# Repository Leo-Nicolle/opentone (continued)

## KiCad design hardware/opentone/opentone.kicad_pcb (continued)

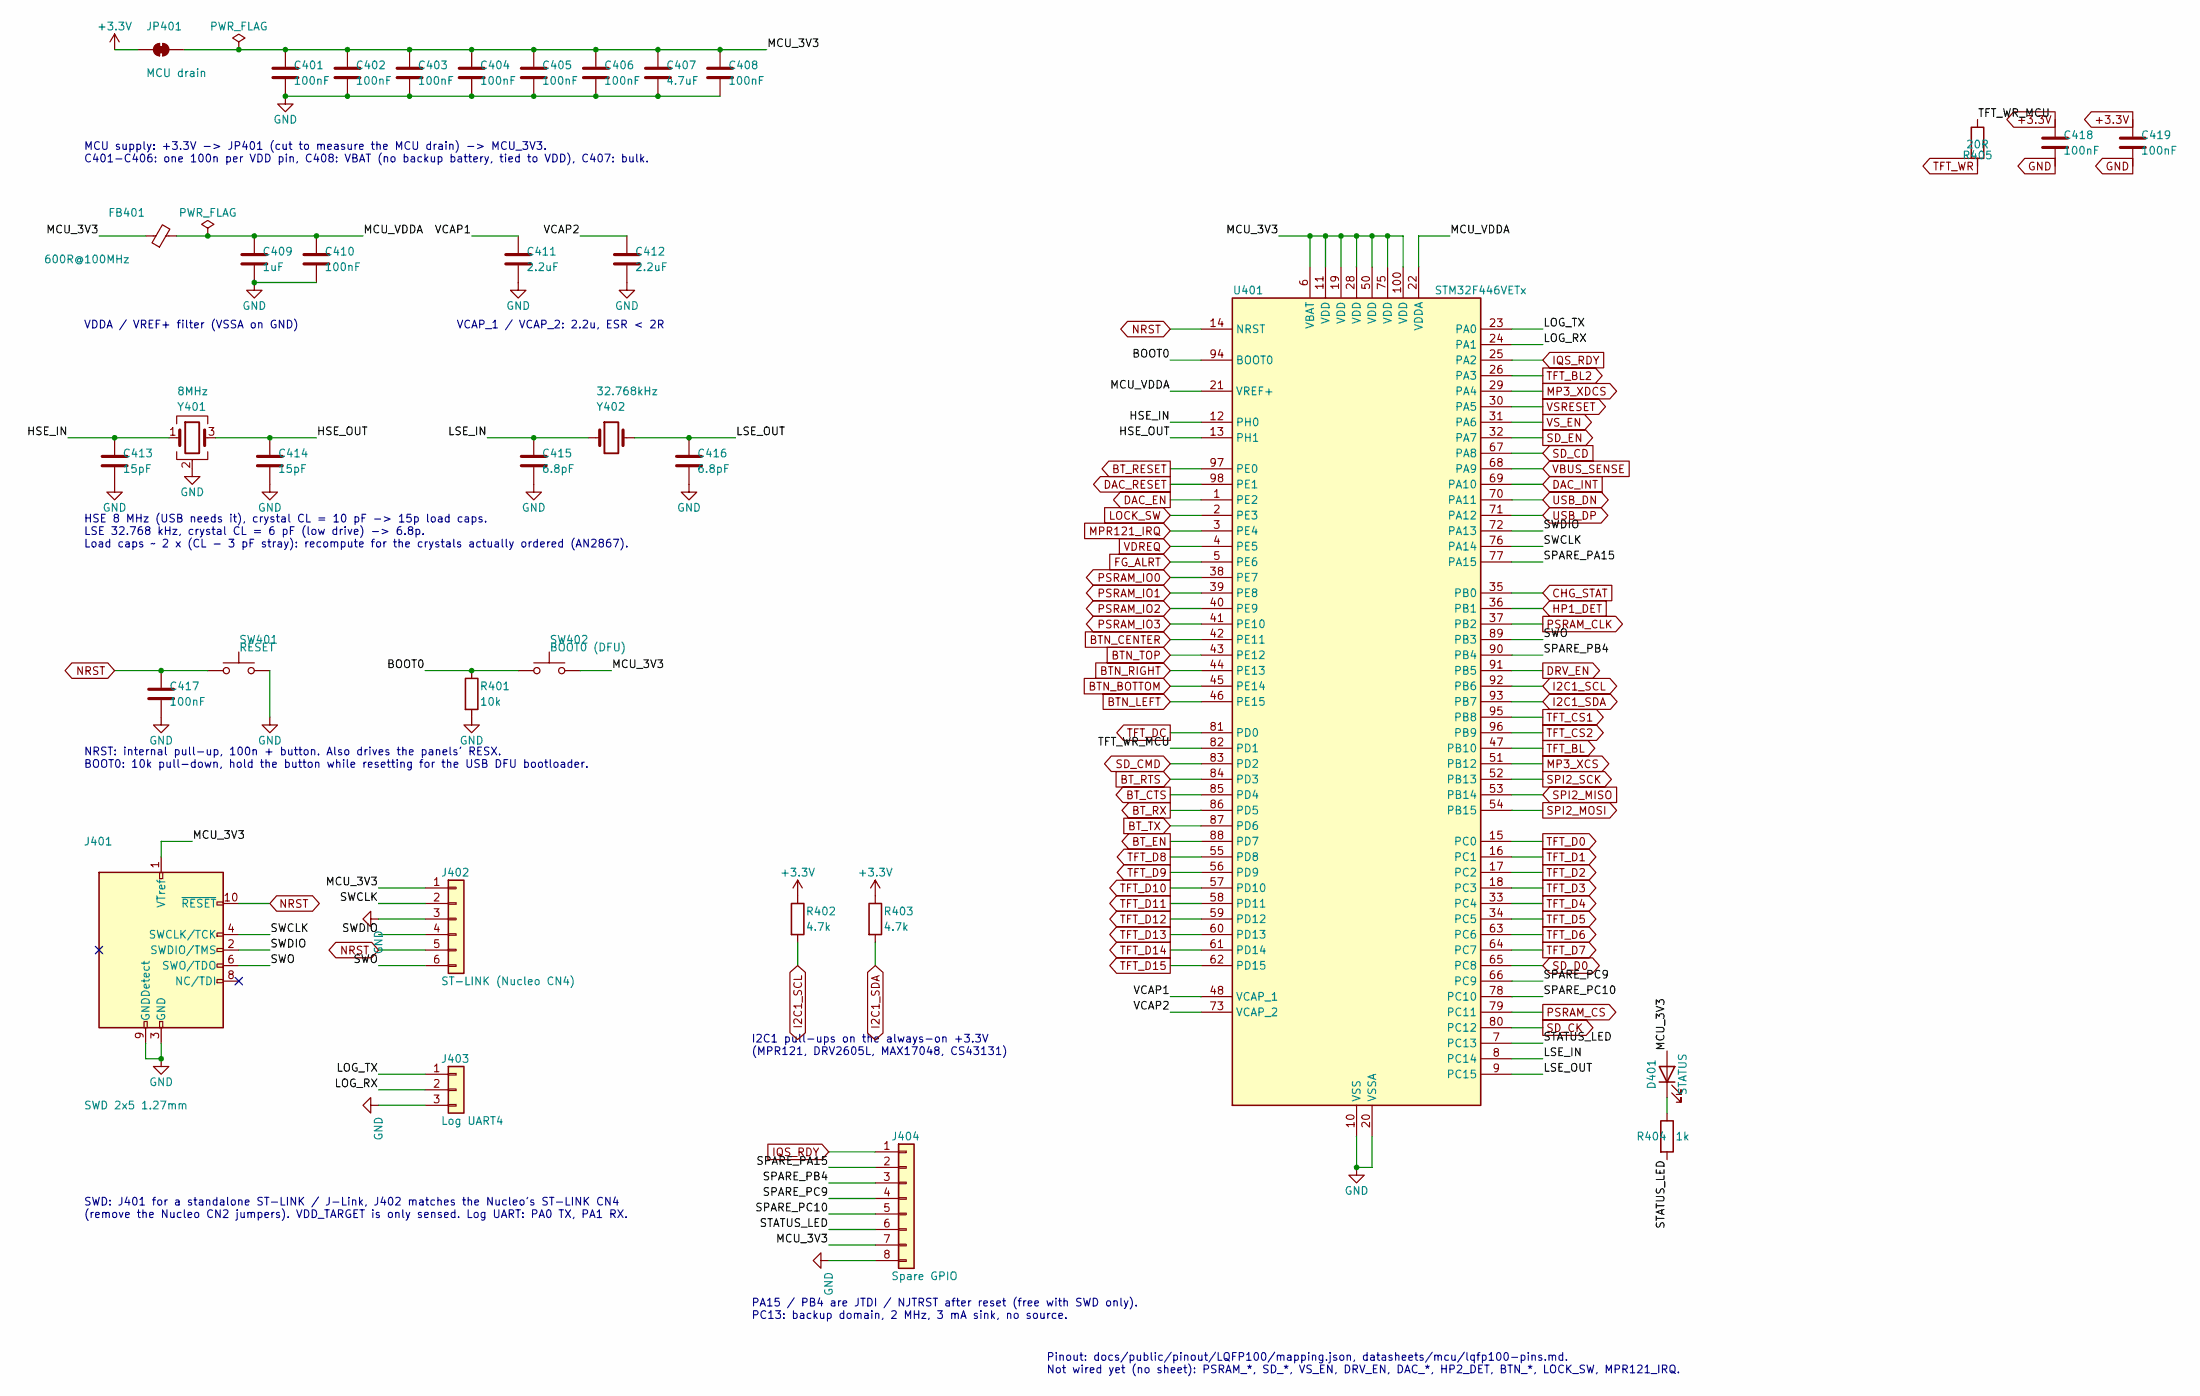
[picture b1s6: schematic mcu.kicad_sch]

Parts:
C401, C402, C403, C404, C405, C406, C408, C410, C417, C418, C419: 100nF; C_0603_1608Metric; Part number CC0603KRX7R9BB104; LCSC C14663
C407: 4.7uF; C_0603_1608Metric; Part number CL10A475KO8NNNC; LCSC C19666
C409: 1uF; C_0603_1608Metric; Part number CL10A105KB8NNNC; LCSC C15849
C411, C412: 2.2uF; C_0603_1608Metric; Part number CL10A225KO8NNNC; LCSC C23630
C413, C414: 15pF; C_0603_1608Metric; Part number CL10C150JB8NNNC; LCSC C1644
C415, C416: 6.8pF; C_0603_1608Metric; Part number 0603CG6R8C500NT; LCSC C1679
D401: STATUS; LED_0603_1608Metric; Part number KT-0603R; LCSC C2286
FB401: 600R@100MHz; L_0603_1608Metric; Part number GZ1608D601TF; LCSC C1002
J401: SWD 2x5 1.27mm; PinHeader_2x05_P1.27mm_Vertical_SMD; Part number 20021121-00010C4LF; LCSC C150517
J402: ST-LINK (Nucleo CN4); PinHeader_1x06_P2.54mm_Vertical
J403: Log UART4; PinHeader_1x03_P2.54mm_Vertical
J404: Spare GPIO; PinHeader_1x08_P2.54mm_Vertical
JP401: MCU drain; SolderJumper-2_P1.3mm_Bridged_RoundedPad1.0x1.5mm
R401: 10k; R_0603_1608Metric; Part number 0603WAF1002T5E; LCSC C25804
R402, R403: 4.7k; R_0603_1608Metric; Part number 0603WAF4701T5E; LCSC C23162
R404: 1k; R_0603_1608Metric; Part number 0603WAF1001T5E; LCSC C21190
R405: 20R; R_0603_1608Metric; Part number 0603WAF200JT5E; LCSC C22950
SW401: RESET; SW_SPST_PTS810; Part number PTS810SJG250SMTRLFS; LCSC C221895
SW402: BOOT0 (DFU); SW_SPST_PTS810; Part number PTS810SJG250SMTRLFS; LCSC C221895
U401: STM32F446VETx; LQFP-100_14x14mm_P0.5mm; Part number STM32F446VET6; LCSC C91929
Y401: 8MHz; Crystal_SMD_3225-4Pin_3.2x2.5mm; Part number K3A080001010; LCSC C19076848
Y402: 32.768kHz; Crystal_SMD_3215-2Pin_3.2x1.5mm; Part number FC-135 32.7680KA-E; LCSC C20340322

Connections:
+3.3V: C418.1, C419.1, JP401.1 (A), R402.1, R403.1; also elsewhere on the board
/MCU/BOOT0: R401.1, SW402.1, U401.94 (BOOT0)
/MCU/HSE_IN: C413.1, U401.12 (PH0), Y401.1
/MCU/HSE_OUT: C414.1, U401.13 (PH1), Y401.3
/MCU/LOG_RX: J403.2, U401.24 (PA1)
/MCU/LOG_TX: J403.1, U401.23 (PA0)
/MCU/LSE_IN: C415.1, U401.8 (PC14), Y402.1
/MCU/LSE_OUT: C416.1, U401.9 (PC15), Y402.2
/MCU/MCU_3V3: C401.1, C402.1, C403.1, C404.1, C405.1, C406.1, C407.1, C408.1, D401.2 (A), FB401.1, J401.1 (VTref), J402.1, J404.7, JP401.2 (B), SW402.2, U401.6 (VBAT), U401.11 (VDD), U401.19 (VDD), U401.28 (VDD), U401.50 (VDD), U401.75 (VDD), U401.100 (VDD)
/MCU/MCU_VDDA: C409.1, C410.1, FB401.2, U401.21 (VREF+), U401.22 (VDDA)
/MCU/SPARE_PA15: J404.2, U401.77 (PA15)
/MCU/SPARE_PB4: J404.3, U401.90 (PB4)
/MCU/SPARE_PC9: J404.4, U401.66 (PC9)
/MCU/SPARE_PC10: J404.5, U401.78 (PC10)
/MCU/STATUS_LED: J404.6, R404.2, U401.7 (PC13)
/MCU/SWCLK: J401.4 (SWCLK/TCK), J402.2, U401.76 (PA14)
/MCU/SWDIO: J401.2 (SWDIO/TMS), J402.4, U401.72 (PA13)
/MCU/SWO: J401.6 (SWO/TDO), J402.6, U401.89 (PB3)
/MCU/TFT_WR_MCU: R405.1, U401.82 (PD1)
/MCU/VCAP1: C411.1, U401.48 (VCAP_1)
/MCU/VCAP2: C412.1, U401.73 (VCAP_2)
BTN_BOTTOM: U401.45 (PE14); also elsewhere on the board
BTN_CENTER: U401.42 (PE11); also elsewhere on the board
BTN_LEFT: U401.46 (PE15); also elsewhere on the board
BTN_RIGHT: U401.44 (PE13); also elsewhere on the board
BTN_TOP: U401.43 (PE12); also elsewhere on the board
BT_CTS: U401.85 (PD4); also elsewhere on the board
BT_EN: U401.88 (PD7); also elsewhere on the board
BT_RESET: U401.97 (PE0); also elsewhere on the board
BT_RTS: U401.84 (PD3); also elsewhere on the board
BT_RX: U401.86 (PD5); also elsewhere on the board
BT_TX: U401.87 (PD6); also elsewhere on the board
CHG_STAT: U401.35 (PB0); also elsewhere on the board
DAC_EN: U401.1 (PE2); also elsewhere on the board
DAC_INT: U401.69 (PA10); also elsewhere on the board
DAC_RESET: U401.98 (PE1); also elsewhere on the board
DRV_EN: U401.91 (PB5); also elsewhere on the board
FG_ALRT: U401.5 (PE6); also elsewhere on the board
GND: C401.2, C402.2, C403.2, C404.2, C405.2, C406.2, C407.2, C408.2, C409.2, C410.2, C411.2, C412.2, C413.2, C414.2, C415.2, C416.2, C417.2, C418.2, C419.2, J401.3 (GND), J401.5 (GND), J401.9 (GNDDetect), J402.3, J403.3, J404.8, R401.2, SW401.2, U401.10 (VSS), U401.20 (VSSA), U401.27 (VSS), U401.49 (VSS), U401.74 (VSS), U401.99 (VSS), Y401.2 (G), Y401.4 (G); also elsewhere on the board
HP1_DET: U401.36 (PB1); also elsewhere on the board
I2C1_SCL: R402.2, U401.92 (PB6); also elsewhere on the board
I2C1_SDA: R403.2, U401.93 (PB7); also elsewhere on the board
IQS_RDY: J404.1, U401.25 (PA2); also elsewhere on the board
LOCK_SW: U401.2 (PE3); also elsewhere on the board
MP3_XCS: U401.51 (PB12); also elsewhere on the board
MP3_XDCS: U401.29 (PA4); also elsewhere on the board
MPR121_IRQ: U401.3 (PE4); also elsewhere on the board
NRST: C417.1, J401.10 (~RESET), J402.5, SW401.1, U401.14 (NRST); also elsewhere on the board
unnamed: D401.1 (K), R404.1
PSRAM_CLK: U401.37 (PB2); also elsewhere on the board
PSRAM_CS: U401.79 (PC11); also elsewhere on the board
PSRAM_IO0: U401.38 (PE7); also elsewhere on the board
PSRAM_IO1: U401.39 (PE8); also elsewhere on the board
PSRAM_IO2: U401.40 (PE9); also elsewhere on the board
PSRAM_IO3: U401.41 (PE10); also elsewhere on the board
SD_CD: U401.67 (PA8); also elsewhere on the board
SD_CK: U401.80 (PC12); also elsewhere on the board
SD_CMD: U401.83 (PD2); also elsewhere on the board
SD_D0: U401.65 (PC8); also elsewhere on the board
SD_EN: U401.32 (PA7); also elsewhere on the board
SPI2_MISO: U401.53 (PB14); also elsewhere on the board
SPI2_MOSI: U401.54 (PB15); also elsewhere on the board
SPI2_SCK: U401.52 (PB13); also elsewhere on the board
TFT_BL: U401.47 (PB10); also elsewhere on the board
TFT_BL2: U401.26 (PA3); also elsewhere on the board
TFT_CS1: U401.95 (PB8); also elsewhere on the board
TFT_CS2: U401.96 (PB9); also elsewhere on the board
TFT_D0: U401.15 (PC0); also elsewhere on the board
TFT_D1: U401.16 (PC1); also elsewhere on the board
TFT_D2: U401.17 (PC2); also elsewhere on the board
TFT_D3: U401.18 (PC3); also elsewhere on the board
TFT_D4: U401.33 (PC4); also elsewhere on the board
TFT_D5: U401.34 (PC5); also elsewhere on the board
TFT_D6: U401.63 (PC6); also elsewhere on the board
TFT_D7: U401.64 (PC7); also elsewhere on the board
TFT_D8: U401.55 (PD8); also elsewhere on the board
TFT_D9: U401.56 (PD9); also elsewhere on the board
TFT_D10: U401.57 (PD10); also elsewhere on the board
TFT_D11: U401.58 (PD11); also elsewhere on the board
TFT_D12: U401.59 (PD12); also elsewhere on the board
TFT_D13: U401.60 (PD13); also elsewhere on the board
TFT_D14: U401.61 (PD14); also elsewhere on the board
TFT_D15: U401.62 (PD15); also elsewhere on the board
TFT_DC: U401.81 (PD0); also elsewhere on the board
TFT_WR: R405.2; also elsewhere on the board
USB_DN: U401.70 (PA11); also elsewhere on the board
USB_DP: U401.71 (PA12); also elsewhere on the board
VBUS_SENSE: U401.68 (PA9); also elsewhere on the board
VDREQ: U401.4 (PE5); also elsewhere on the board
VSRESET: U401.30 (PA5); also elsewhere on the board
VS_EN: U401.31 (PA6); also elsewhere on the board

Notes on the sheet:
Pinout: docs/public/pinout/LQFP100/mapping.json, datasheets/mcu/lqfp100-pins.md. Not wired yet (no sheet): PSRAM_*, SD_*, VS_EN, DRV_EN, DAC_*, HP2_DET, BTN_*, LOCK_SW, MPR121_IRQ.
I2C1 pull-ups on the always-on +3.3V (MPR121, DRV2605L, MAX17048, CS43131)
VDDA / VREF+ filter (VSSA on GND)
MCU supply: +3.3V -> JP401 (cut to measure the MCU drain) -> MCU_3V3. C401-C406: one 100n per VDD pin, C408: VBAT (no backup battery, tied to VDD), C407: bulk.
PA15 / PB4 are JTDI / NJTRST after reset (free with SWD only). PC13: backup domain, 2 MHz, 3 mA sink, no source.
NRST: internal pull-up, 100n + button. Also drives the panels' RESX. BOOT0: 10k pull-down, hold the button while resetting for the USB DFU bootloader.
HSE 8 MHz (USB needs it), crystal CL = 10 pF -> 15p load caps. LSE 32.768 kHz, crystal CL = 6 pF (low drive) -> 6.8p. Load caps ~ 2 x (CL - 3 pF stray): recompute for the crystals actually ordered (AN2867).
VCAP_1 / VCAP_2: 2.2u, ESR < 2R
SWD: J401 for a standalone ST-LINK / J-Link, J402 matches the Nucleo's ST-LINK CN4 (remove the Nucleo CN2 jumpers). VDD_TARGET is only sensed. Log UART: PA0 TX, PA1 RX.

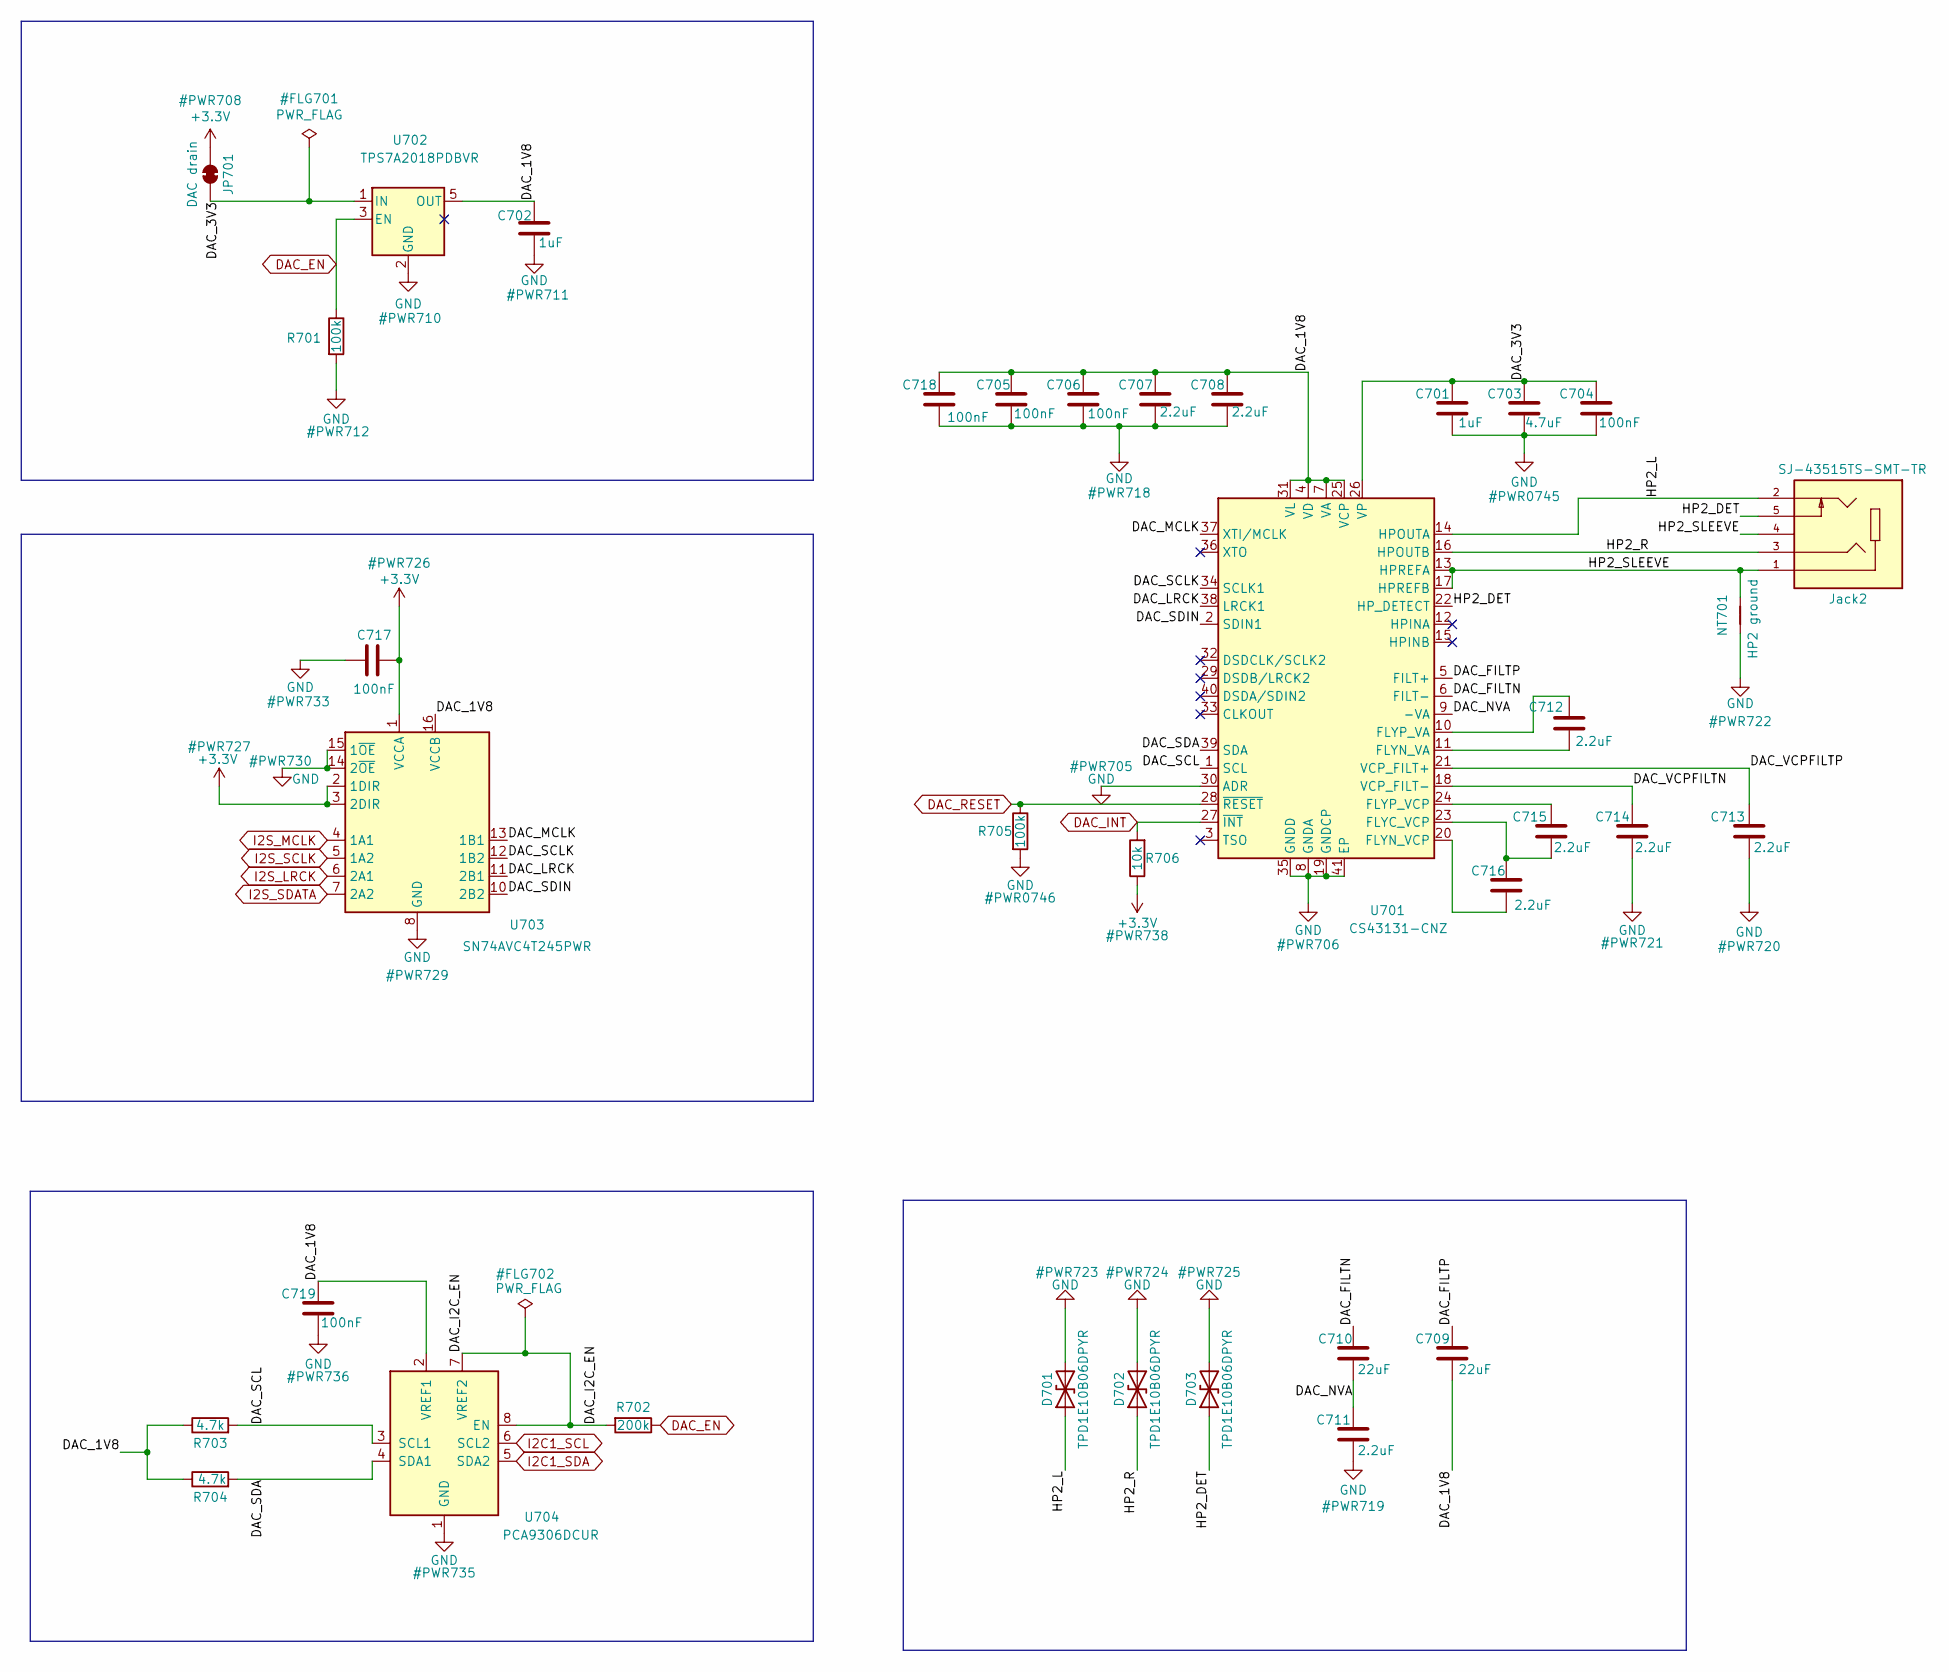
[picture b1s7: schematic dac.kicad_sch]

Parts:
C701, C702: 1uF; C_0603_1608Metric; Part number CL10A105KB8NNNC; LCSC C15849
C703: 4.7uF; C_0603_1608Metric; Part number CL10A475KO8NNNC; LCSC C19666
C704, C705, C706, C717, C718, C719: 100nF; C_0603_1608Metric; Part number CC0603KRX7R9BB104; LCSC C14663
C707, C708, C711, C712, C713, C714, C715, C716: 2.2uF; C_0603_1608Metric; Part number CL10A225KO8NNNC; LCSC C23630
C709, C710: 22uF; C_0805_2012Metric; Part number CL21A226MAQNNNE; LCSC C45783
D701, D702, D703: TPD1E10B06DPYR; Texas_DPY0002A_0.6x1mm_P0.65mm; Part number TPD1E10B06DPYR; LCSC C48260
JP701: DAC drain; SolderJumper-2_P1.3mm_Bridged_RoundedPad1.0x1.5mm
Jack2: SJ-43515TS-SMT-TR; CUI_SJ-43515TS-SMT-TR; Part number SJ-43515TS-SMT-TR; LCSC C5353507
NT701: HP2 ground; NetTie-2_SMD_Pad0.5mm
R701, R705: 100k; R_0603_1608Metric; Part number 0603WAF1003T5E; LCSC C25803
R702: 200k; R_0603_1608Metric; Part number 0603WAF2003T5E; LCSC C25811
R703, R704: 4.7k; R_0603_1608Metric; Part number 0603WAF4701T5E; LCSC C23162
R706: 10k; R_0603_1608Metric; Part number 0603WAF1002T5E; LCSC C25804
U701: CS43131-CNZ; TQFN-40-1EP_5x5mm_P0.4mm_EP3.5x3.5mm; Part number CS43131-CNZ; LCSC C1554759
U702: TPS7A2018PDBVR; SOT-23-5; Part number TPS7A2018PDBVR; LCSC C963430
U703: SN74AVC4T245PWR; TSSOP-16_4.4x5mm_P0.65mm; Part number SN74AVC4T245PWR; LCSC C81461
U704: PCA9306DCUR; VSSOP-8_2.3x2mm_P0.5mm; Part number PCA9306DCUR; LCSC C33196

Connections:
+3.3V: C717.1, JP701.1 (A), R706.1, U703.1 (VCCA), U703.2 (1DIR), U703.3 (2DIR); also elsewhere on the board
/DAC/DAC_1V8: C702.1, C705.1, C706.1, C707.1, C708.1, C709.2, C718.1, C719.1, R703.1, R704.1, U701.4 (VD), U701.7 (VA), U701.25 (VCP), U701.31 (VL), U702.5 (OUT), U703.16 (VCCB), U704.2 (VREF1)
/DAC/DAC_3V3: C701.1, C703.1, C704.1, JP701.2 (B), U701.26 (VP), U702.1 (IN)
/DAC/DAC_FILTN: C710.1, U701.6 (FILT-)
/DAC/DAC_FILTP: C709.1, U701.5 (FILT+)
/DAC/DAC_I2C_EN: R702.2, U704.7 (VREF2), U704.8 (EN)
/DAC/DAC_LRCK: U701.38 (LRCK1), U703.11 (2B1)
/DAC/DAC_MCLK: U701.37 (XTI/MCLK), U703.13 (1B1)
/DAC/DAC_NVA: C710.2, C711.1, U701.9 (-VA)
/DAC/DAC_SCL: R703.2, U701.1 (SCL), U704.3 (SCL1)
/DAC/DAC_SCLK: U701.34 (SCLK1), U703.12 (1B2)
/DAC/DAC_SDA: R704.2, U701.39 (SDA), U704.4 (SDA1)
/DAC/DAC_SDIN: U701.2 (SDIN1), U703.10 (2B2)
/DAC/DAC_VCPFILTN: C714.1, U701.18 (VCP_FILT-)
/DAC/DAC_VCPFILTP: C713.1, U701.21 (VCP_FILT+)
/DAC/HP2_DET: D703.1 (A1), Jack2.5, U701.22 (HP_DETECT)
/DAC/HP2_L: D701.1 (A1), Jack2.2, U701.14 (HPOUTA)
/DAC/HP2_R: D702.1 (A1), Jack2.3, U701.16 (HPOUTB)
/DAC/HP2_SLEEVE: Jack2.1, Jack2.4, NT701.2, U701.13 (HPREFA), U701.17 (HPREFB)
DAC_EN: R701.1, R702.1, U702.3 (EN); also elsewhere on the board
DAC_INT: R706.2, U701.27 (~INT); also elsewhere on the board
DAC_RESET: R705.1, U701.28 (~RESET); also elsewhere on the board
GND: C701.2, C702.2, C703.2, C704.2, C705.2, C706.2, C707.2, C708.2, C711.2, C713.2, C714.2, C717.2, C718.2, C719.2, D701.2 (A2), D702.2 (A2), D703.2 (A2), NT701.1, R701.2, R705.2, U701.8 (GNDA), U701.19 (GNDCP), U701.30 (ADR), U701.35 (GNDD), U701.41 (EP), U702.2 (GND), U703.8 (GND), U703.9 (GND), U703.14 (2~OE), U703.15 (1~OE), U704.1 (GND); also elsewhere on the board
I2C1_SCL: U704.6 (SCL2); also elsewhere on the board
I2C1_SDA: U704.5 (SDA2); also elsewhere on the board
I2S_LRCK: U703.6 (2A1); also elsewhere on the board
I2S_MCLK: U703.4 (1A1); also elsewhere on the board
I2S_SCLK: U703.5 (1A2); also elsewhere on the board
I2S_SDATA: U703.7 (2A2); also elsewhere on the board
unnamed: C715.2, C716.1, U701.23 (FLYC_VCP)
unnamed: C712.2, U701.11 (FLYN_VA)
unnamed: C716.2, U701.20 (FLYN_VCP)
unnamed: C712.1, U701.10 (FLYP_VA)
unnamed: C715.1, U701.24 (FLYP_VCP)

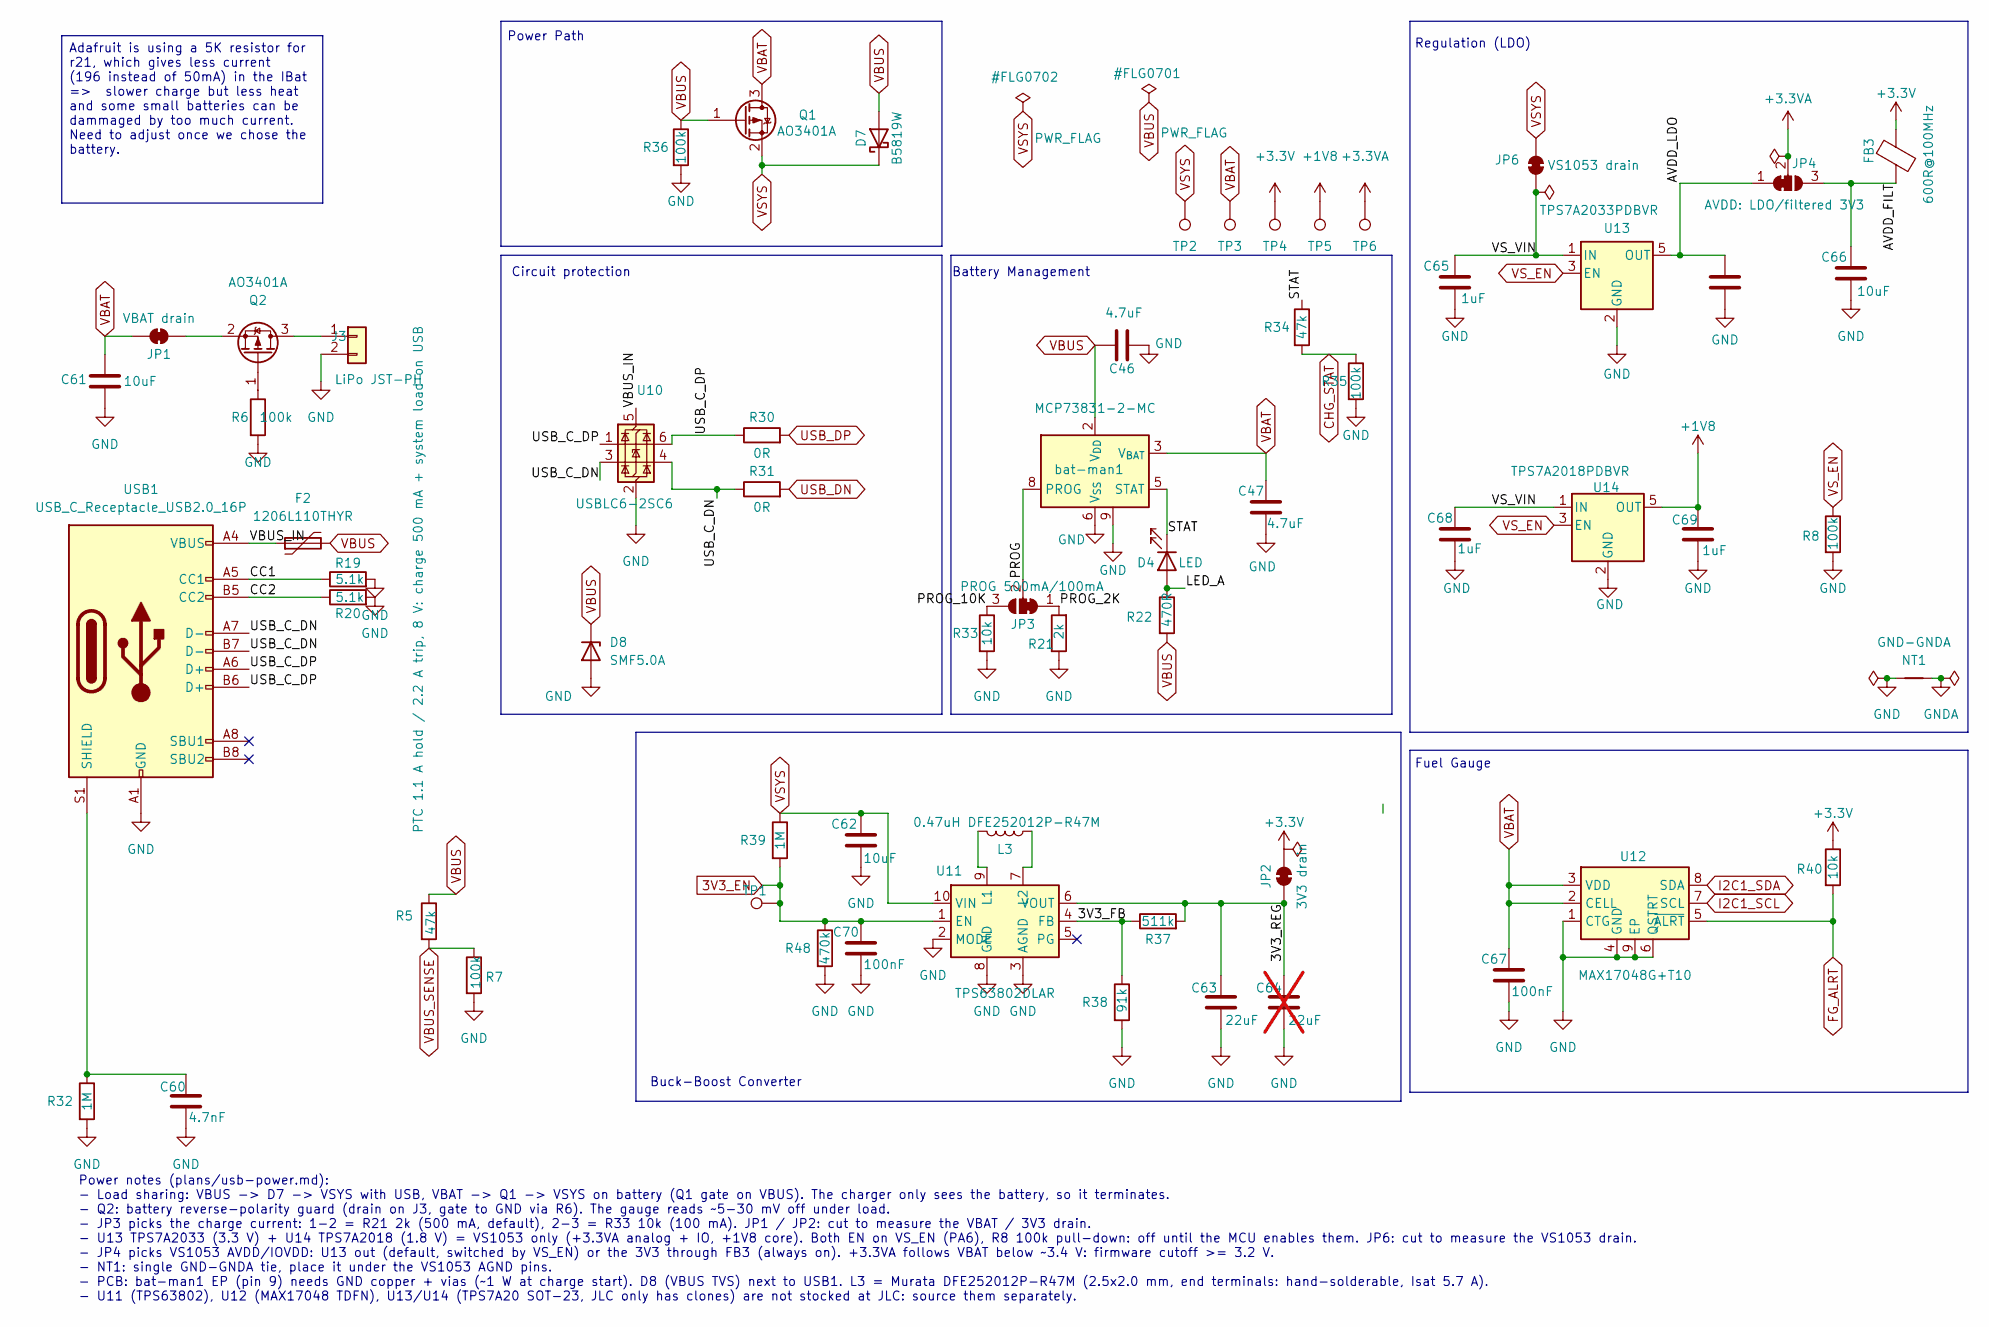
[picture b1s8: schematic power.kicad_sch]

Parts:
C46, C47: 4.7uF; C_0805_2012Metric; Part number CL21A475KAQNNNE; LCSC C1779
C52, C65, C68, C69: 1uF; C_0603_1608Metric; Part number CL10A105KB8NNNC; LCSC C15849
C60: 4.7nF; C_0603_1608Metric; Part number 0603B472K500NT; LCSC C53987
C61, C62: 10uF; C_0805_2012Metric; Part number CL21A106KAYNNNE; LCSC C15850
C63: 22uF; C_0805_2012Metric; Part number CL21A226MAQNNNE; LCSC C45783
C64: 22uF; C_0805_2012Metric; Part number CL21A226MAQNNNE; LCSC C45783; not fitted
C66: 10uF; C_0603_1608Metric; Part number CL10A106KP8NNNC; LCSC C19702
C67, C70: 100nF; C_0603_1608Metric; Part number CC0603KRX7R9BB104; LCSC C14663
D4: LED; LED_0603_1608Metric; Part number KT-0603R; LCSC C2286
D7: B5819W; D_SOD-123; Part number B5819W SL; LCSC C8598
D8: SMF5.0A; D_SOD-123F; Part number SMF5.0A; LCSC C151296
F2: 1206L110THYR; Fuse_1206_3216Metric; Part number 1206L110THYR; LCSC C126818
FB3: 600R@100MHz; L_0603_1608Metric; Part number GZ1608D601TF; LCSC C1002
J3: LiPo JST-PH; JST_PH_S2B-PH-SM4-TB_1x02-1MP_P2.00mm_Horizontal; Part number S2B-PH-SM4-TB(LF)(SN); LCSC C295747
JP1: VBAT drain; SolderJumper-2_P1.3mm_Bridged_RoundedPad1.0x1.5mm
JP2: 3V3 drain; SolderJumper-2_P1.3mm_Bridged_RoundedPad1.0x1.5mm
JP3: PROG 500mA/100mA; SolderJumper-3_P1.3mm_Bridged12_RoundedPad1.0x1.5mm
JP4: AVDD: LDO/filtered 3V3; SolderJumper-3_P1.3mm_Bridged12_RoundedPad1.0x1.5mm
JP6: VS1053 drain; SolderJumper-2_P1.3mm_Bridged_RoundedPad1.0x1.5mm
L3: 0.47uH DFE252012P-R47M; L_1008_2520Metric_Pad1.43x2.20mm_HandSolder; Part number DFE252012P-R47M=P2; LCSC C237552
NT1: GND-GNDA; NetTie-2_SMD_Pad0.5mm
Q1, Q2: AO3401A; SOT-23; Part number AO3401A; LCSC C15127
R5, R34: 47k; R_0603_1608Metric; Part number 0603WAF4702T5E; LCSC C25819
R6, R7, R8, R35, R36: 100k; R_0603_1608Metric; Part number 0603WAF1003T5E; LCSC C25803
R19, R20: 5.1k; R_0603_1608Metric; Part number 0603WAF5101T5E; LCSC C23186
R21: 2k; R_0603_1608Metric; Part number 0603WAF2001T5E; LCSC C22975
R22: 470R; R_0603_1608Metric; Part number 0603WAF4700T5E; LCSC C23179
R30, R31: 0R; R_0603_1608Metric; Part number 0603WAF0000T5E; LCSC C21189
R32, R39: 1M; R_0603_1608Metric; Part number 0603WAF1004T5E; LCSC C22935
R33, R40: 10k; R_0603_1608Metric; Part number 0603WAF1002T5E; LCSC C25804
R37: 511k; R_0603_1608Metric; Part number 0603WAF5113T5E; LCSC C23194
R38: 91k; R_0603_1608Metric; Part number 0603WAF9102T5E; LCSC C23265
R48: 470k; R_0603_1608Metric; Part number 0603WAF4703T5E; LCSC C23178
TP1: 3V3_EN; TestPoint_Pad_D1.0mm
TP2: VSYS; TestPoint_Pad_D1.0mm
TP3: VBAT; TestPoint_Pad_D1.0mm
TP4: +3.3V; TestPoint_Pad_D1.0mm
TP5: +1V8; TestPoint_Pad_D1.0mm
TP6: +3.3VA; TestPoint_Pad_D1.0mm
U10: USBLC6-2SC6; SOT-23-6; Part number USBLC6-2SC6; LCSC C7519
U11: TPS63802DLAR; Texas_DLA0010A_VSON-HR-10_2x3mm_P0.5mm; Part number TPS63802DLAR; LCSC C2845237
U12: MAX17048G+T10; TDFN-8-1EP_2x2mm_P0.5mm_EP0.8x1.2mm; Part number MAX17048G+T10; LCSC C2682616
U13: TPS7A2033PDBVR; SOT-23-5; Part number TPS7A2033PDBVR; LCSC C2862740
U14: TPS7A2018PDBVR; SOT-23-5; Part number TPS7A2018PDBVR; LCSC C963430
USB1: USB_C_Receptacle_USB2.0_16P; USB_C_Receptacle_HRO_TYPE-C-31-M-12; Part number TYPE-C-31-M-12; LCSC C165948
bat-man1: MCP73831-2-MC; DFN-8-1EP_3x2mm_P0.5mm_EP1.7x1.4mm; Part number MCP73831-2ACI/MC; LCSC C150772

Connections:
3V3_EN: C70.1, R39.2, R48.1, TP1.1 (1_1), U11.1 (EN); also elsewhere on the board
+1V8: C69.1, TP5.1 (1_1), U14.5 (OUT); also elsewhere on the board
+3.3V: FB3.1, JP2.2 (B), R40.1, TP4.1 (1_1); also elsewhere on the board
+3.3VA: JP4.2 (C), TP6.1 (1_1); also elsewhere on the board
/Power/3V3_FB: R37.1, R38.1, U11.4 (FB)
/Power/3V3_REG: C63.1, C64.1, JP2.1 (A), R37.2, U11.6 (VOUT)
/Power/AVDD_FILT: C66.1, FB3.2, JP4.3 (B)
/Power/AVDD_LDO: C52.1, JP4.1 (A), U13.5 (OUT)
/Power/CC1: R19.1, USB1.A5 (CC1)
/Power/CC2: R20.1, USB1.B5 (CC2)
/Power/LED_A: D4.2 (A), R22.1
/Power/PROG: JP3.2 (C), bat-man1.8 (PROG)
/Power/PROG_2K: JP3.1 (A), R21.2
/Power/PROG_10K: JP3.3 (B), R33.1
/Power/STAT: D4.1 (K), R34.1, bat-man1.5 (STAT)
/Power/USB_C_DN: R31.1, U10.3 (I/O2), U10.4 (I/O2), USB1.A7 (D-), USB1.B7 (D-)
/Power/USB_C_DP: R30.1, U10.1 (I/O1), U10.6 (I/O1), USB1.A6 (D+), USB1.B6 (D+)
/Power/VBUS_IN: F2.1, U10.5 (VBUS), USB1.A4 (VBUS), USB1.A9 (VBUS), USB1.B4 (VBUS), USB1.B9 (VBUS)
/Power/VS_VIN: C65.1, C68.1, JP6.2 (B), U13.1 (IN), U14.1 (IN)
CHG_STAT: R34.2, R35.1; also elsewhere on the board
FG_ALRT: R40.2, U12.5 (~ALRT); also elsewhere on the board
GND: C46.1, C47.2, C52.2, C60.2, C61.2, C62.2, C63.2, C64.2, C65.2, C66.2, C67.2, C68.2, C69.2, C70.2, D8.2 (A), J3.2, NT1.1, R6.2, R7.2, R8.2, R19.2, R20.2, R21.1, R32.2, R33.2, R35.2, R36.2, R38.2, R48.2, U10.2 (GND), U11.2 (MODE), U11.3 (AGND), U11.8 (GND), U12.1 (CTG), U12.4 (GND), U12.6 (QSTRT), U12.9 (EP), U13.2 (GND), U14.2 (GND), USB1.A1 (GND), USB1.A12 (GND), USB1.B1 (GND), USB1.B12 (GND), bat-man1.6 (V_{SS}), bat-man1.9; also elsewhere on the board
GNDA: NT1.2; also elsewhere on the board
I2C1_SCL: U12.7 (SCL); also elsewhere on the board
I2C1_SDA: U12.8 (SDA); also elsewhere on the board
unnamed: J3.1, Q2.3 (D)
unnamed: JP1.1 (A), Q2.2 (S)
unnamed: Q2.1 (G), R6.1
unnamed: L3.2, U11.9 (L1)
unnamed: L3.1, U11.7 (L2)
unnamed: C60.1, R32.1, USB1.S1 (SHIELD)
USB_DN: R31.2; also elsewhere on the board
USB_DP: R30.2; also elsewhere on the board
VBAT: C47.1, C61.1, C67.1, JP1.2 (B), Q1.3 (D), TP3.1 (1_1), U12.2 (CELL), U12.3 (VDD), bat-man1.3 (V_{BAT}), bat-man1.4 (V_{BAT})
VBUS: C46.2, D7.2 (A), D8.1 (K), F2.2, Q1.1 (G), R5.1, R22.2, R36.1, bat-man1.1 (V_{DD}), bat-man1.2 (V_{DD})
VBUS_SENSE: R5.2, R7.1; also elsewhere on the board
VSYS: C62.1, D7.1 (K), JP6.1 (A), Q1.2 (S), R39.1, TP2.1 (1_1), U11.10 (VIN); also elsewhere on the board
VS_EN: R8.1, U13.3 (EN), U14.3 (EN); also elsewhere on the board

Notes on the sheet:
Buck-Boost Converter
Fuel Gauge
Power Path
Circuit protection
Power notes (plans/usb-power.md): - Load sharing: VBUS -> D7 -> VSYS with USB, VBAT -> Q1 -> VSYS on battery (Q1 gate on VBUS). The charger only sees the battery, so it terminates. - Q2: battery reverse-polarity guard (drain on J3, gate to GND via R6). The gauge reads ~5-30 mV off under load. - JP3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
Battery Management
Regulation (LDO)
Adafruit is using a 5K resistor for r21, which gives less current (196 instead of 50mA) in the IBat => slower charge but less heat and some small batteries can be dammaged by too much current. Need to adjust once we chose the battery.

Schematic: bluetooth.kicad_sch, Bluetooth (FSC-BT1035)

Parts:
C101: 10uF; C_0603_1608Metric; Part number CL10A106KP8NNNC; LCSC C19702
C102, C103: 100nF; C_0603_1608Metric; Part number CC0603KRX7R9BB104; LCSC C14663
C104, C105, C107, C113: 1uF; C_0603_1608Metric; Part number CL10A105KB8NNNC; LCSC C15849
C108: 1nF; C_0603_1608Metric; Part number CL10B102KB8NNNC; LCSC C1588
D101: LED0; LED_0603_1608Metric; Part number KT-0603R; LCSC C2286
D102: LED1; LED_0603_1608Metric; Part number KT-0603R; LCSC C2286
JP5: BT 3V3 drain; SolderJumper-2_P1.3mm_Bridged_RoundedPad1.0x1.5mm
JP101: BYPASS; SolderJumper-2_P1.3mm_Open_RoundedPad1.0x1.5mm
Q101: BSS138; SOT-23; Part number BSS138LT1G; LCSC C82045
R51, R52, R53, R102: 0R; R_0603_1608Metric; Part number 0603WAF0000T5E; LCSC C21189
R101, R112: 100k; R_0603_1608Metric; Part number 0603WAF1003T5E; LCSC C25803
R111: 2k; R_0603_1608Metric; Part number 0603WAF2001T5E; LCSC C22975
R113, R114: 1k; R_0603_1608Metric; Part number 0603WAF1001T5E; LCSC C21190
U101: FSC-BT1035; fsc-bt1035; Part number FSC-BT1035
U102: TPS22917; SOT-23-6; Part number TPS22917DBVR; LCSC C2681320

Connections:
+3.3V: JP5.1 (A); also elsewhere on the board
/Bluetooth/BT_1V8: C104.1, U101.35 (1.8V_OUT)
/Bluetooth/BT_3V3: C101.1, C102.1, C103.1, C113.1, JP101.2 (B), R102.2, R111.1, R113.1, R114.1, U101.33 (VBAT_IN), U101.36 (VDD_IO), U102.6 (VOUT)
/Bluetooth/BT_3V3_IN: C107.1, JP5.2 (B), JP101.1 (A), R101.1, U102.1 (VIN)
/Bluetooth/BT_3V3_OUT: C105.1, U101.31 (VDD_USB/3.3V_OUT)
/Bluetooth/BT_I2S_BCLK: R51.2, U101.4 (PCM_CLK/PIO16)
/Bluetooth/BT_I2S_LRCK: R52.2, U101.7 (PCM_SYNC/PIO17)
/Bluetooth/BT_I2S_SDIN: R53.2, U101.5 (PCM_IN/PIO19)
/Bluetooth/BT_LED0: D101.1 (K), U101.17 (AIO0/LED0)
/Bluetooth/BT_LED1: D102.1 (K), U101.18 (AIO1/LED1)
/Bluetooth/BT_PON_G: C113.2, Q101.1 (G), R112.1
/Bluetooth/BT_SW_CT: C108.1, U102.4 (CT)
/Bluetooth/BT_SW_QOD: R102.1, U102.5 (QOD)
/Bluetooth/BT_SYS_CTRL: Q101.3 (D), R111.2, U101.34 (SYS_CTRL)
BT_CTS: U101.15 (BT_CTS/PIO3); also elsewhere on the board
BT_EN: R101.2, U102.3 (ON); also elsewhere on the board
BT_RESET: U101.8 (RESET); also elsewhere on the board
BT_RTS: U101.16 (BT_RTS/PIO2); also elsewhere on the board
BT_RX: U101.14 (BT_RX/PIO4); also elsewhere on the board
BT_TX: U101.13 (BT_TX/PIO5); also elsewhere on the board
GND: C101.2, C102.2, C103.2, C104.2, C105.2, C107.2, C108.2, Q101.2 (S), R112.2, U101.1 (GND), U101.22 (GND), U101.32 (GND), U101.50 (GND), U101.52 (GND), U102.2 (GND); also elsewhere on the board
I2S_LRCK: R52.1; also elsewhere on the board
I2S_SCLK: R51.1; also elsewhere on the board
I2S_SDATA: R53.1; also elsewhere on the board
unnamed: D101.2 (A), R113.2
unnamed: D102.2 (A), R114.2

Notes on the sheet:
I2S from the VS1053 (module = I2S slave). 0R: unfit to free the bus for the DAC. PCM_MCLK_OUT (pin 9) is an output and not needed: left open.
VIN cap CT (slew) EN pull-up QOD (DNP if bypassed)
When BT_3V3 rises, Q101 holds SYS_CTRL low ~100 ms, then releases it -> the module boots.
MCU (STM32F446VET6), see docs/public/pinout/LQFP100/mapping.json: - BT_RX <- PD5 USART2_TX - BT_TX -> PD6 USART2_RX - BT_CTS <- PD4 USART2_RTS - BT_RTS -> PD3 USART2_CTS - BT_EN <- PD7 (high = BT powered, pulled up) - BT_RESET <- PE0, open-drain (RESET# has an internal pull-up) Before pulling BT_EN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
Supply: +3.3V -> JP5 (cut to measure the BT drain) -> TPS22917
Auto power-on (datasheet ref. circuit)
Status LEDs (LED pads are open-drain)
Power: +3.3V -> JP5 -> TPS22917 load switch (BT_EN) -> VBAT_IN and VDD_IO (module accepts 3.0-4.2 V, all I/O at 3.3 V logic). Switching BT_3V3 on boots the module (auto power-on circuit on SYS_CTRL). No USB: VCHG, VCHG_SENSE and USB_D+/D- are left open.
Bypass: close JP101 and leave the 0R (QOD) unfitted, or QOD would discharge the 3V3 rail while the switch is off.
BT power switch: TPS22917 (same part as the SD card switch)
FSC-BT1035 Bluetooth module, on the test board
Decoupling (place close to the module)

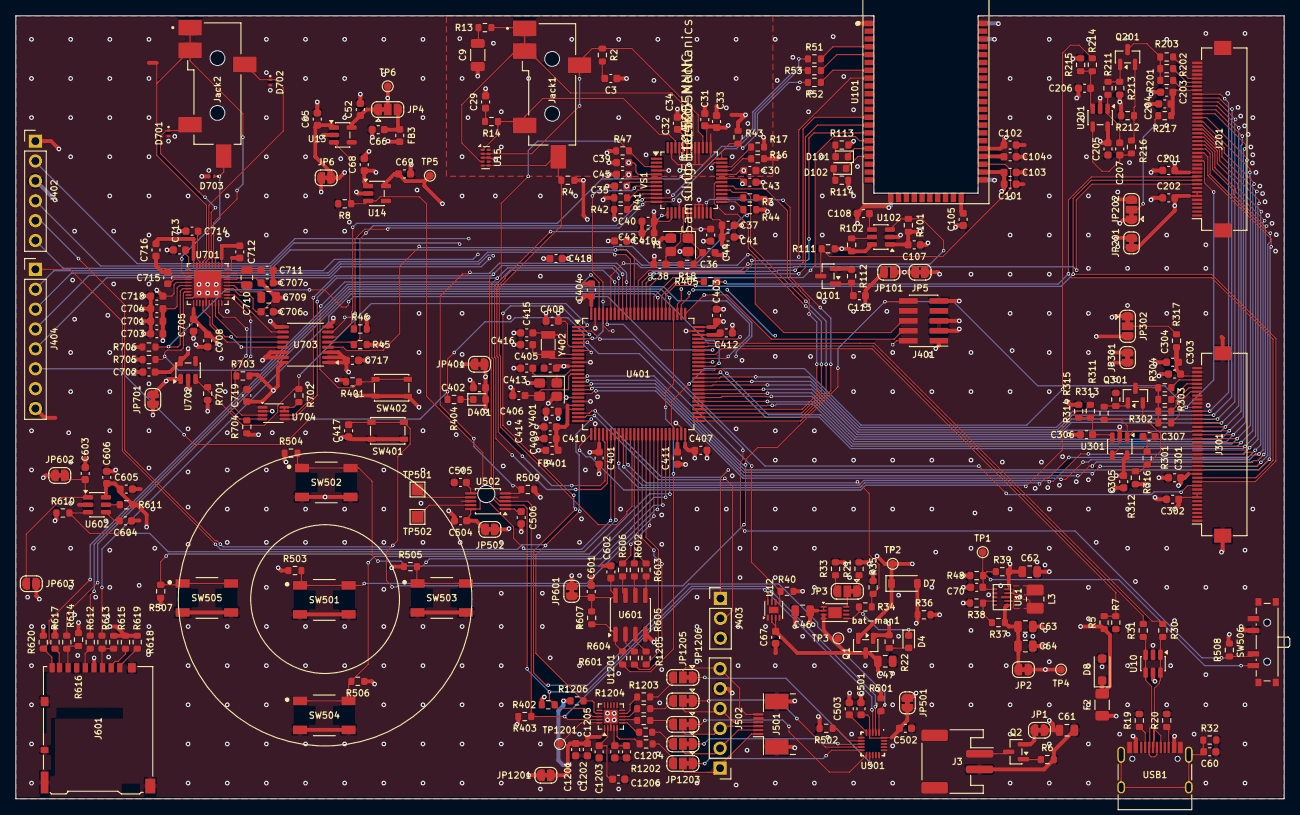
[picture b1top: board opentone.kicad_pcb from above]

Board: 4 copper layers, 162.0 x 100.0 mm, 319 parts (0 on the bottom side), 248 nets.
